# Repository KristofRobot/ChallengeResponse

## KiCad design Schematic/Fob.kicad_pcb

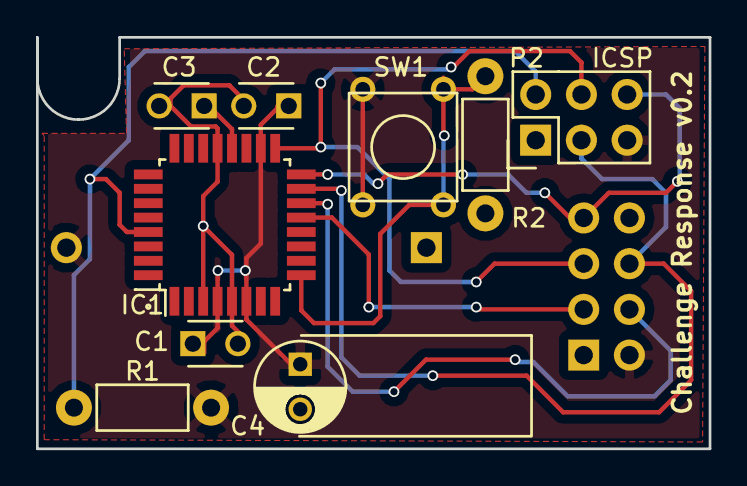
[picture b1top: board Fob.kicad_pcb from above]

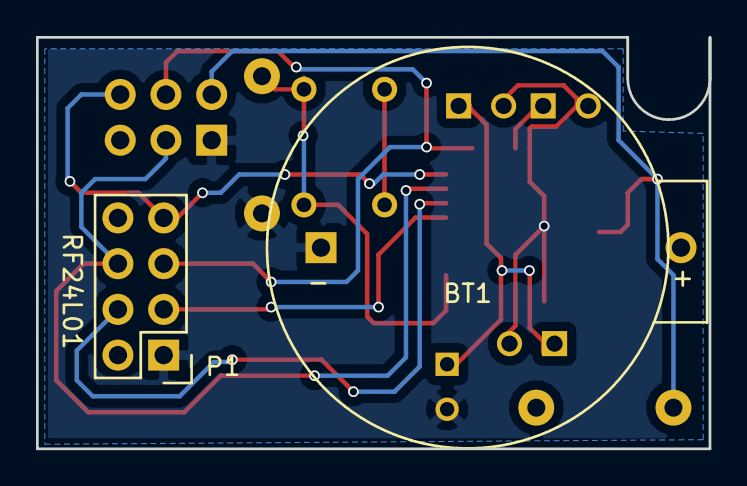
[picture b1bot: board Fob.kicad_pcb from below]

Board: 2 copper layers, 37.4 x 22.9 mm, 11 parts (2 on the bottom side), 10 nets.

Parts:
BT1: CR2032
C1: 100n; C_Disc_P2.5
C2, C3: 100n; C_Disc_P2
C4: 10uF; C_Radial_D5_L6_P2.5_length
IC1: ATMEGA328-P; TQFP-32_7x7mm_Pitch0.8mm
P1: RF24L01; Pin_Header_RF24L01
P2: ICSP; Pin_Header_Straight_2x03
R1, R2: 10K; Resistor_Horizontal_RM7mm
SW1: SW_PUSH; SW_PUSH_6mm

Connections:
GND: BT1.2, C1.2, C2.2, C3.2, C4.2, IC1.3, IC1.5, IC1.21, P1.1, P2.1, R2.1
unnamed: C3.1, IC1.20
unnamed: IC1.9, R2.2, SW1.1
unnamed: IC1.13, P1.3
unnamed: IC1.14, P1.4
unnamed: IC1.15, P1.6, P2.3
unnamed: IC1.16, P1.7, P2.6
unnamed: IC1.17, P1.5, P2.4
unnamed: IC1.29, P2.2, R1.2
VCC: BT1.1, C1.1, C2.1, C4.1, IC1.4, IC1.6, IC1.18, P1.2, P2.5, R1.1, SW1.2

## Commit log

2016-02-27 first version
2016-03-06 schematic: v0.1
2016-03-06 Adding radio power down statements
2016-04-10 PCB: version 2
2016-05-01 Firmware: version 1.0
2016-12-28 Transmitter: implemented double click
2016-12-28 Receiver: added additional comments about random generator
2016-12-28 Randomness testing collateral
